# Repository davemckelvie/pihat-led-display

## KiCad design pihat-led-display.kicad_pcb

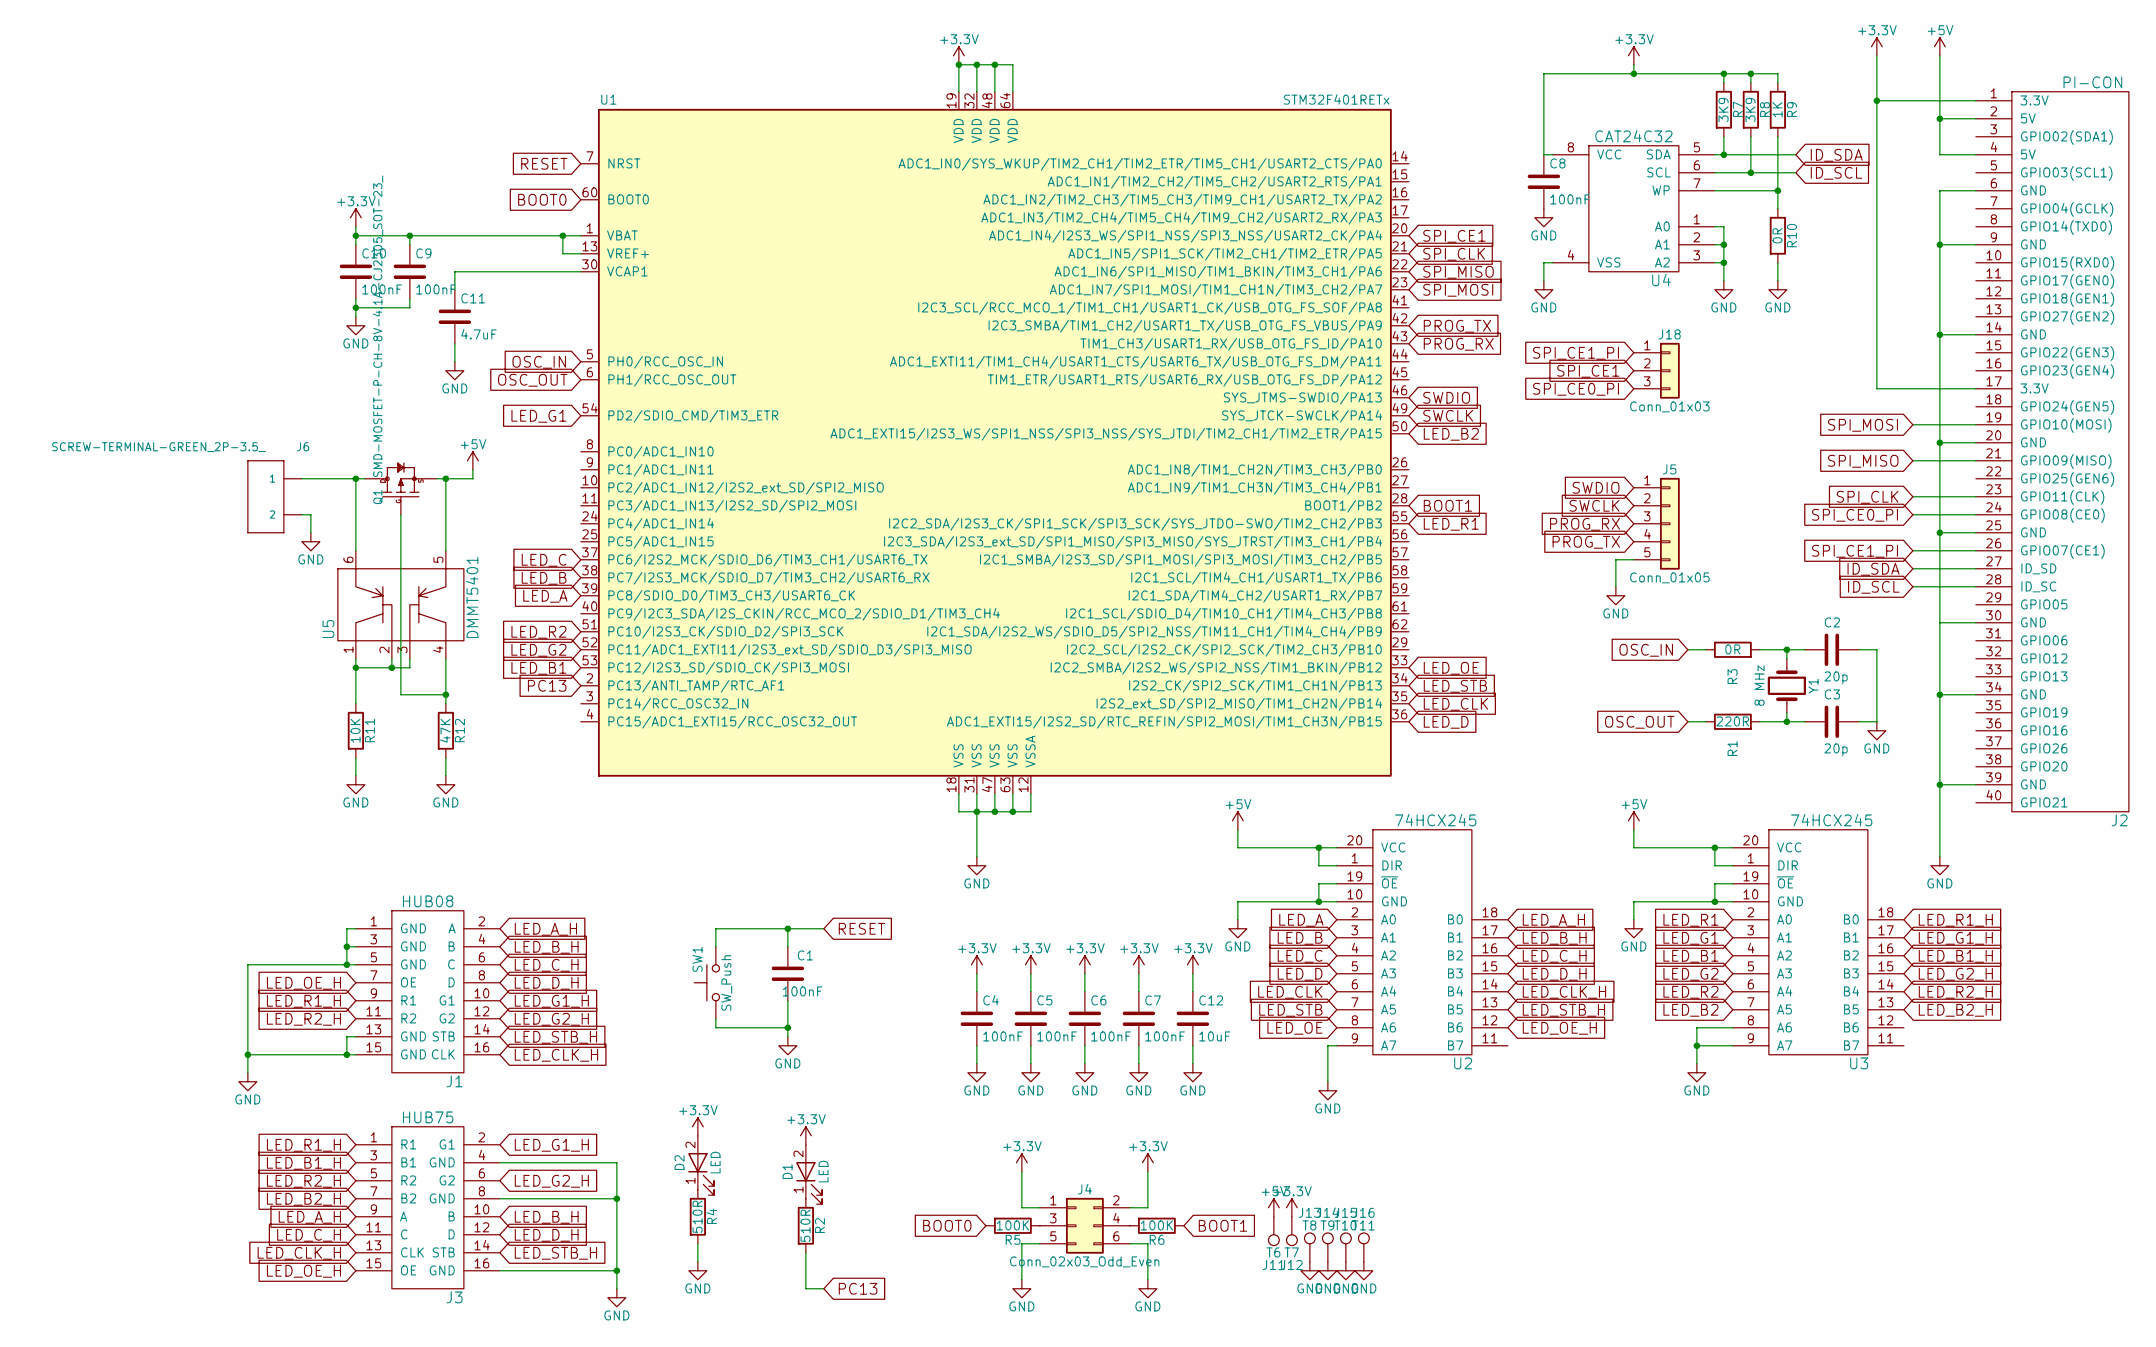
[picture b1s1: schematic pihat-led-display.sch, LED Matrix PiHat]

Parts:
C1, C4, C5, C6, C7, C8, C9, C10: 100nF; C_0603
C2, C3: 20p; C_0603
C11: 4.7uF; C_0603
C12: 10uF; C_0603
D1, D2: LED; LED_0805
J1: HUB08; IDC-Header_2x08_Pitch2.54mm_Straight
J2: PI-CON; Pin_Header_Straight_2x20_Pitch2.54mm
J3: HUB75; IDC-Header_2x08_Pitch2.54mm_Straight
J4: Conn_02x03_Odd_Even; Pin_Header_Straight_2x03_Pitch2.54mm
J5: Conn_01x05; Pin_Header_Straight_1x05_Pitch2.54mm
J6: SCREW-TERMINAL-GREEN_2P-3.5_; H2-3.5-7.0X7.0MM
J11: T6; Test_Point_Pad_d1.0mm
J12: T7; Test_Point_Pad_d1.0mm
J13: T8; Test_Point_Pad_2.0x2.0mm
J14: T9; Test_Point_Pad_2.0x2.0mm
J15: T10; Test_Point_Pad_2.0x2.0mm
J16: T11; Test_Point_Pad_2.0x2.0mm
J18: Conn_01x03; Pin_Header_Straight_1x03_Pitch2.54mm
Q1: SMD-MOSFET-P-CH-8V-4.1A-CJ2305_SOT-23_; SOT-23; MPN CJ2305
R1: 220R; R_0603
R2, R4: 510R; R_0603
R3, R10: 0R; R_0603
R5, R6: 100K; R_0603
R7, R8: 3K9; R_0603
R9: 1K; R_0603
R11: 10K; R_0603
R12: 47K; R_0603
SW1: SW_Push; SW_SPST_SKQG
U1: STM32F401RETx; LQFP-64_10x10mm_Pitch0.5mm
U2, U3: 74HCX245; TSSOP-20_4.4x6.5mm_Pitch0.65mm
U4: CAT24C32; SOIC-8_3.9x4.9mm_Pitch1.27mm
U5: DMMT5401; SOT-23-6
Y1: 8 MHz; Crystal_HC49-4H_Vertical

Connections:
+3V3: C4.1, C5.1, C6.1, C7.1, C8.1, C9.1, C10.1, C12.1, D1.2 (A), D2.2 (A), J2.1 (3.3V), J2.17 (3.3V), J4.1, J4.2, J12.1, R7.1, R8.1, R9.1, U1.1 (VBAT), U1.13 (VREF+), U1.19 (VDD), U1.32 (VDD), U1.48 (VDD), U1.64 (VDD), U4.8 (VCC)
+5V: J2.2 (5V), J2.4 (5V), J11.1, Q1.2 (S), U2.1 (DIR), U2.20 (VCC), U3.1 (DIR), U3.20 (VCC), U5.5
BOOT0: R5.2, U1.60 (BOOT0)
BOOT1: R6.1, U1.28 (BOOT1/PB2)
GND: C1.1, C2.1, C3.1, C4.2, C5.2, C6.2, C7.2, C8.2, C9.2, C10.2, C11.2, C12.2, J1.1 (GND), J1.3 (GND), J1.5 (GND), J1.13 (GND), J1.15 (GND), J2.6 (GND), J2.9 (GND), J2.14 (GND), J2.20 (GND), J2.25 (GND), J2.34 (GND), J2.39 (GND), J3.4 (GND), J3.8 (GND), J3.16 (GND), J4.5, J4.6, J5.5, J6.2, J13.1, J14.1, J15.1, J16.1, R4.2, R10.2, R11.2, R12.2, SW1.1, U1.12 (VSSA), U1.18 (VSS), U1.31 (VSS), U1.47 (VSS), U1.63 (VSS), U2.9 (A7), U2.10 (GND), U2.19 (~OE), U3.8 (A6), U3.9 (A7), U3.10 (GND), U3.19 (~OE), U4.1 (A0), U4.2 (A1), U4.3 (A2), U4.4 (VSS)
ID_SCL: J2.28 (ID_SC), R8.2, U4.6 (SCL)
ID_SDA: J2.27 (ID_SD), R7.2, U4.5 (SDA)
LED_A: U1.39 (PC8/SDIO_D0/TIM3_CH3/USART6_CK), U2.2 (A0)
LED_A_H: J1.2 (A), J3.9 (A), U2.18 (B0)
LED_B: U1.38 (PC7/I2S3_MCK/SDIO_D7/TIM3_CH2/USART6_RX), U2.3 (A1)
LED_B1: U1.53 (PC12/I2S3_SD/SDIO_CK/SPI3_MOSI), U3.4 (A2)
LED_B1_H: J3.3 (B1), U3.16 (B2)
LED_B2: U1.50 (ADC1_EXTI15/I2S3_WS/SPI1_NSS/SPI3_NSS/S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), U3.7 (A5)
LED_B2_H: J3.7 (B2), U3.13 (B5)
LED_B_H: J1.4 (B), J3.10 (B), U2.17 (B1)
LED_C: U1.37 (PC6/I2S2_MCK/SDIO_D6/TIM3_CH1/USART6_TX), U2.4 (A2)
LED_CLK: U1.35 (I2S2_ext_SD/SPI2_MISO/TIM1_CH2N/PB14), U2.6 (A4)
LED_CLK_H: J1.16 (CLK), J3.13 (CLK), U2.14 (B4)
LED_C_H: J1.6 (C), J3.11 (C), U2.16 (B2)
LED_D: U1.36 (ADC1_EXTI15/I2S2_SD/RTC_REFIN/SPI2_MOSI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), U2.5 (A3)
LED_D_H: J1.8 (D), J3.12 (D), U2.15 (B3)
LED_G1: U1.54 (PD2/SDIO_CMD/TIM3_ETR), U3.3 (A1)
LED_G1_H: J1.10 (G1), J3.2 (G1), U3.17 (B1)
LED_G2: U1.52 (PC11/ADC1_EXTI11/I2S3_ext_SD/SDIO_D3/SP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), U3.5 (A3)
LED_G2_H: J1.12 (G2), J3.6 (G2), U3.15 (B3)
LED_OE: U1.33 (I2C2_SMBA/I2S2_WS/SPI2_NSS/TIM1_BKIN/PB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), U2.8 (A6)
LED_OE_H: J1.7 (OE), J3.15 (OE), U2.12 (B6)
LED_R1: U1.55 (I2C2_SDA/I2S3_CK/SPI1_SCK/SPI3_SCK/SYS_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), U3.2 (A0)
LED_R1_H: J1.9 (R1), J3.1 (R1), U3.18 (B0)
LED_R2: U1.51 (PC10/I2S3_CK/SDIO_D2/SPI3_SCK), U3.6 (A4)
LED_R2_H: J1.11 (R2), J3.5 (R2), U3.14 (B4)
LED_STB: U1.34 (I2S2_CK/SPI2_SCK/TIM1_CH1N/PB13), U2.7 (A5)
LED_STB_H: J1.14 (STB), J3.14 (STB), U2.13 (B5)
unnamed: C2.2, R3.2, Y1.1
unnamed: C3.2, R1.2, Y1.2
unnamed: C11.1, U1.30 (VCAP1)
unnamed: D1.1 (K), R2.1
unnamed: D2.1 (K), R4.1
unnamed: J4.3, R5.1
unnamed: J4.4, R6.2
unnamed: J6.1, Q1.3 (D), U5.6
unnamed: Q1.1 (G), R12.1, U5.4
unnamed: R9.2, R10.1, U4.7 (WP)
unnamed: R11.1, U5.1, U5.2, U5.3
OSC_IN: R3.1, U1.5 (PH0/RCC_OSC_IN)
OSC_OUT: R1.1, U1.6 (PH1/RCC_OSC_OUT)
PC13: R2.2, U1.2 (PC13/ANTI_TAMP/RTC_AF1)
PROG_RX: J5.3, U1.43 (TIM1_CH3/USART1_RX/USB_OTG_FS_ID/PA10)
PROG_TX: J5.4, U1.42 (I2C3_SMBA/TIM1_CH2/USART1_TX/USB_OTG_FS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)
RESET: C1.2, SW1.2, U1.7 (NRST)
SPI_CE0_PI: J2.24 (GPIO08(CE0)), J18.3
SPI_CE1: J18.2, U1.20 (ADC1_IN4/I2S3_WS/SPI1_NSS/SPI3_NSS/USAR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)
SPI_CE1_PI: J2.26 (GPIO07(CE1)), J18.1
SPI_CLK: J2.23 (GPIO11(CLK)), U1.21 (ADC1_IN5/SPI1_SCK/TIM2_CH1/TIM2_ETR/PA5)
SPI_MISO: J2.21 (GPIO09(MISO)), U1.22 (ADC1_IN6/SPI1_MISO/TIM1_BKIN/TIM3_CH1/P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)
SPI_MOSI: J2.19 (GPIO10(MOSI)), U1.23 (ADC1_IN7/SPI1_MOSI/TIM1_CH1N/TIM3_CH2/P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)
SWCLK: J5.2, U1.49 (SYS_JTCK-SWCLK/PA14)
SWDIO: J5.1, U1.46 (SYS_JTMS-SWDIO/PA13)

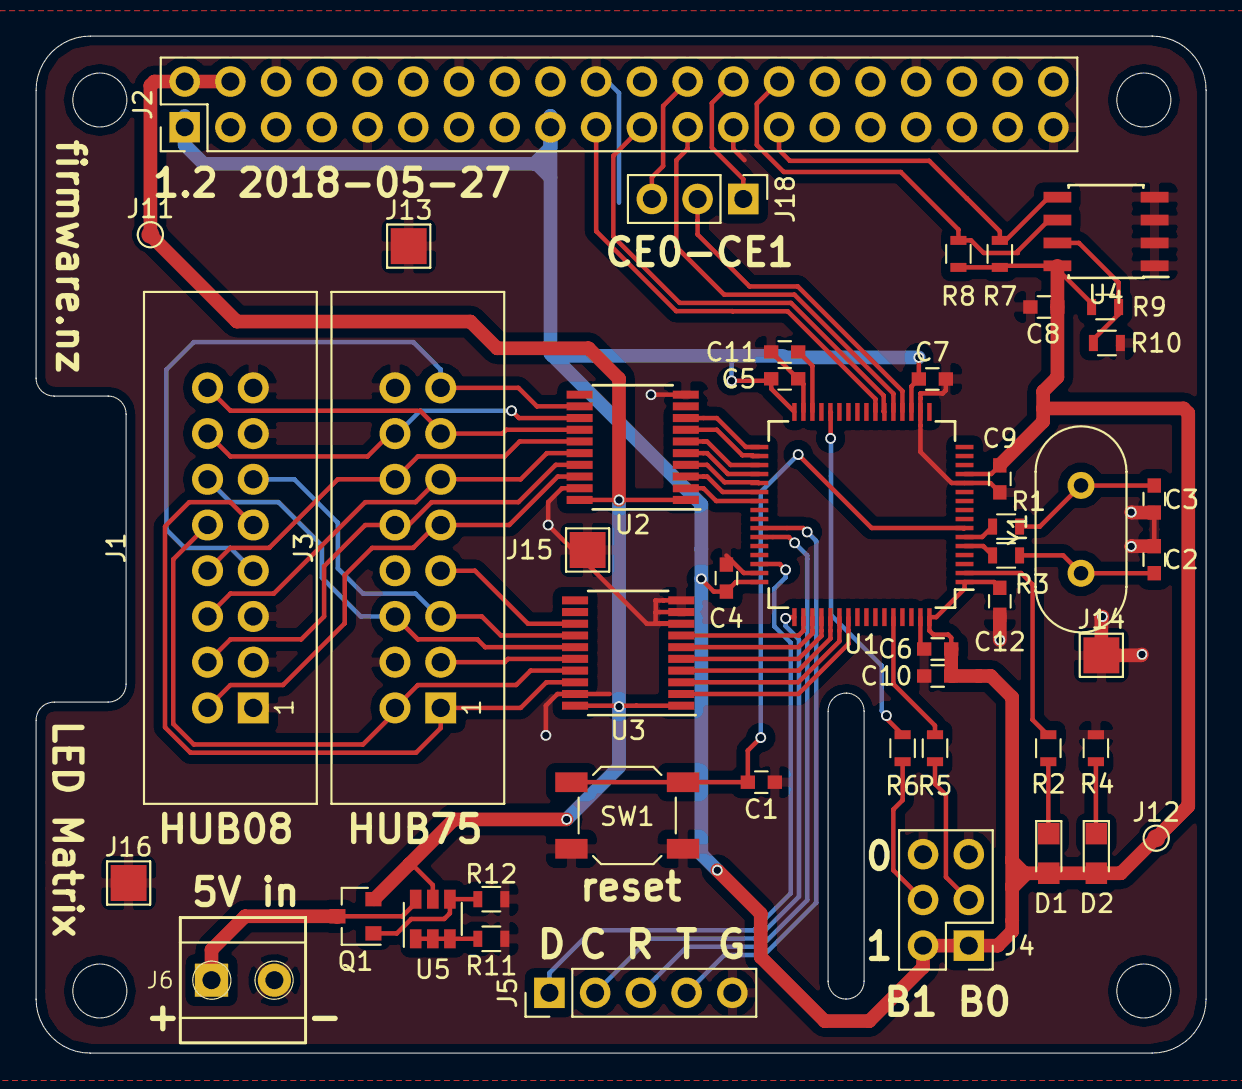
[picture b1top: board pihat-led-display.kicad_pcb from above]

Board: 2 copper layers, 65.0 x 56.5 mm, 47 parts (0 on the bottom side), 58 nets.
